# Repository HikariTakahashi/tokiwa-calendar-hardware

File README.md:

# 概要

「部屋を丸ごとリマインダーにする」タスク管理に特化したカレンダーアプリ、『TokiWa Calendar』のレポジトリです。
従来のタスク管理ツールが抱える「通知の見逃し」「タスクの後回し」という根源的な課題に対し、ソフトウェアとハードウェアの融合で解決する新しいタスク管理システムです。デジタル上のタスクを現実世界の「光・音・モノの動き」に変換し、ユーザーの物理環境に直接働きかけることで、確実な行動を促します。
『ToKiWa calendar』は、ソフトウェアによる「認知」のサポートと、ハードウェアによる物理的な「行動喚起」を組み合わせ、“わかっていても行動できない”という課題（意図と行動の乖離）を解消します。タスク管理に「環境そのものをデザインする」という新たな選択肢を提示します。
## 関連URL
YouTube動画:
https://www.youtube.com/watch?v=OgA2TAeWcS0 <br>
URL:
https://www.tokiwa-calendar.com/welcome <br>
# 導入準備
## 前提

動作には以上の~~四つ~~三つのレポジトリのインストールが必要です

**フロントエンド**:https://github.com/HikariTakahashi/tokiwa-calendar-frontend <br>
**バックエンド**:https://github.com/HikariTakahashi/tokiwa-calendar-backend <br>
**ハードウェア**:https://github.com/HikariTakahashi/tokiwa-calendar-hardware  ← いまここ <br>
~~**DiscordBot**~~:https://github.com/HikariTakahashi/tokiwa-calendar-discordbot

## 起動準備(フロントエンド)

1. レポジトリのクローン

```bash
git clone https://github.com/HikariTakahashi/simple-calendar-frontend.git
```

2. 必要なもののインストール

```bash
// フロントエンドのプロジェクトに移動(いつもの開き方でOK)
cd simple-calendar-frontend

// Node.jsのパッケージ管理システムをインストール
npm install
```

3. .env ファイルの書き込み
   .env ファイルの中身を担当者から貰ってください
   注:アップデート等により.env ファイルは頻繁に変更されるため、こまめに確認してください。

## 起動準備(バックエンド)

1. レポジトリのクローン

```bash
git clone https://github.com/HikariTakahashi/tokiwa-calendar-backend.git
```

2. バックエンドのプロジェクトに移動(個人のいつもの開き方で OK)

```bash
cd tokiwa-calendar-backend
```

3. .env ファイルの書き込み
   .env ファイルの中身を担当者から貰ってください
   注:アップデート等により.env ファイルは頻繁に変更されるため、こまめに確認してください。

## 起動準備(ハードウェア)
1. PlatformIO IDEの導入
VSCode の「拡張機能」から PlatformIO IDE を検索してインストール
2. レポジトリのクローン
```bash
git clone https://github.com/HikariTakahashi/tokiwa-calendar-hardware.git
```
3. ハードウェアのプロジェクトに移動(個人のいつもの開き方でOK)
```bash
cd tokiwa-calendar-hardware
```
3. PCにESP32C6を接続
4. ファームウェアを書き込む
　コンパイルボタンを押す
5. 外部から操作したい端末でアクセスポイントに接続
```bash 
http://192.168.4.1/
```
3. ssidとパスワードを入力しwifiに接続
　シリアルモニターを確認
　```bash
　http://<シリアルモニターに表示されたIPアドレス>/control
```

## 開発サーバーの起動

1. バックエンド起動（Go 言語）

```bash
// バックエンドのターミナルで実行
go run --tags=local .
```

注: 以前は `go run main.go` でしたが、ファイル分割により `go run .`に変更されました。プロジェクト内のすべての .go ファイルがビルド対象になります。
注 2: `go run .`からさらに`go run --tags=local .`に変更されました。

2. フロントエンド起動（Nuxt.js）

```bash
// フロントエンドのターミナルで実行
npm run dev
```

3. 開発用のサーバーにアクセス

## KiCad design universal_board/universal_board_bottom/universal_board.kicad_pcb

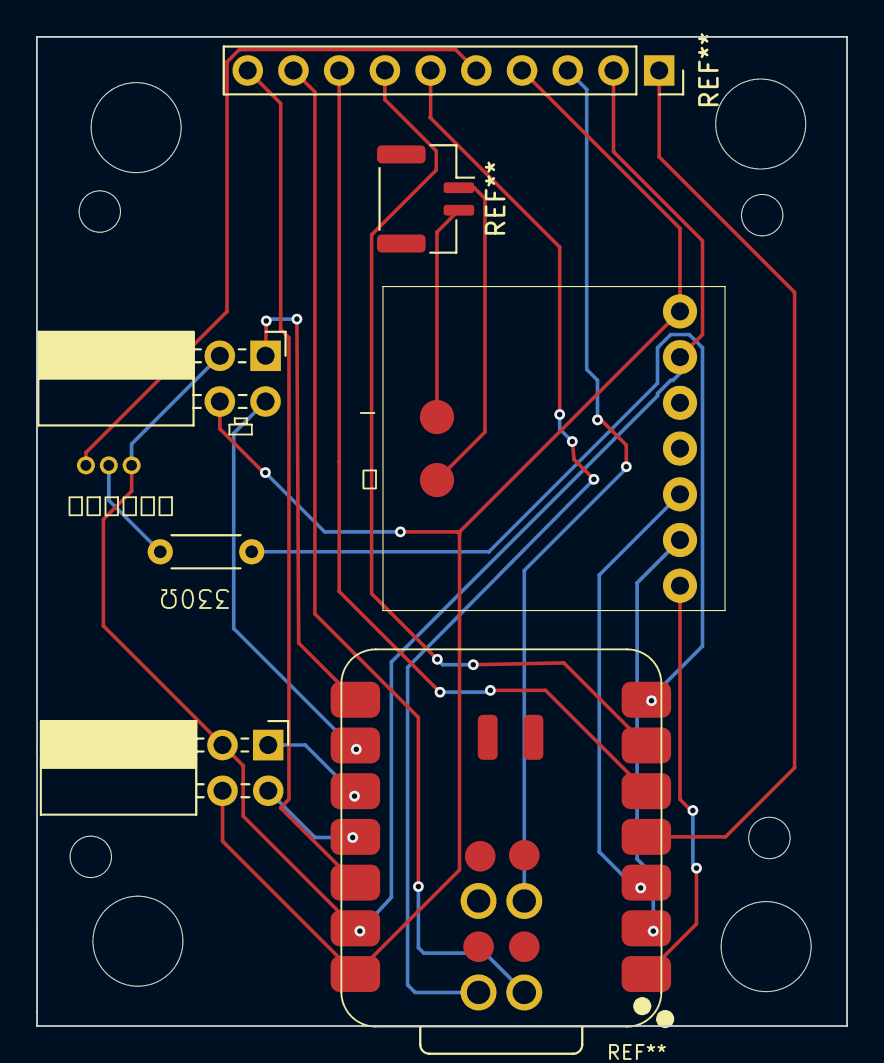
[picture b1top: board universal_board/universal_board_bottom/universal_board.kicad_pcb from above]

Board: 2 copper layers, 45.0 x 54.9 mm, 12 parts (0 on the bottom side), 2 nets.

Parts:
1, 2, 2#2, 3, 4, 5, 6, 7, 8, 9: (no value)
dadada: PinSocket_2x02_P2.54mm_Horizontal
dawdad: PinSocket_2x02_P2.54mm_Horizontal

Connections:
5V: dadada.4, dawdad.2
GND: 1.6, dadada.2, dawdad.2

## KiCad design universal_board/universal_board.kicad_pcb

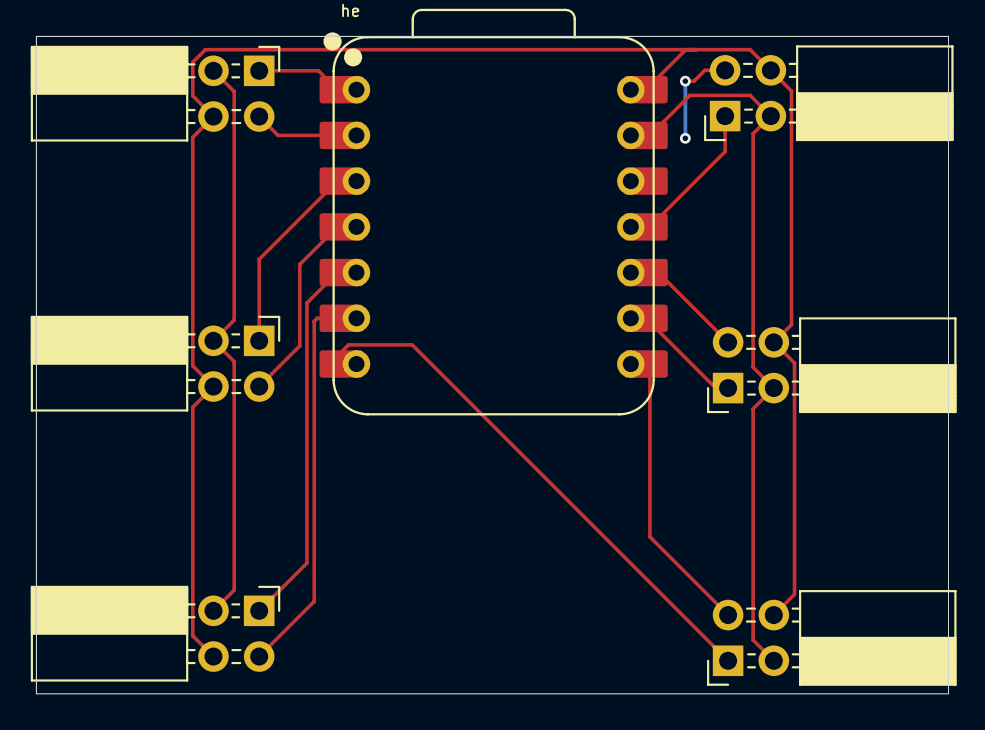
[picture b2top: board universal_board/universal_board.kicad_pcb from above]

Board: 2 copper layers, 50.7 x 36.5 mm, 6 parts (0 on the bottom side), 11 nets.

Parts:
ad: PinSocket_2x02_P2.54mm_Horizontal
adadad: PinSocket_2x02_P2.54mm_Horizontal
dadada: PinSocket_2x02_P2.54mm_Horizontal
dawdad: PinSocket_2x02_P2.54mm_Horizontal
fdsf: PinSocket_2x02_P2.54mm_Horizontal
he: XIAO-ESP32-C6-DIP; XIAO-ESP32C6-DIP

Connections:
1: dawdad.1, he.1
2: dawdad.eeeeee, he.2
3: ad.1, he.3
4: ad.3, he.4
5: adadad.1, he.5
5V: ad.4, adadad.4, dadada.4, dawdad.2, fdsf.4, he.14
6: adadad.3, he.6
9: fdsf.1, he.9
10: fdsf.3, he.10
11: dadada.1, he.11
GND: ad.2, adadad.2, dadada.2, dawdad.2, fdsf.2, he.13

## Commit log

2025-06-12 test
    testできる
2025-08-19 universal_ver0.1
2025-08-21 update/README.md
2025-08-24 board manu
2025-08-27 case and MQTT
2025-09-06 board
2025-09-06 kari
2025-09-06 board2
2025-09-12 new design
2025-09-12 owari1
2025-09-12 OLED 0.1
